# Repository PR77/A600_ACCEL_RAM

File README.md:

# A600_ACCEL_RAM
Design attempt for an Amiga 600 over CPU (PLCC) 68000 Accelerator including 1.5MB FastRAM (... or is it SlowRAM) and 0.5MB MapROM support.

# Warning
This design has not been compliance tested and will not be. It may cause damage to your A600. I take no responsibility for this. I accept no responsibility for any damage to any equipment that results from the use of this design and its components. IT IS ENTIRELY AT YOUR OWN RISK!

# Overview
The main purpose of this design was to develop a simple, affordable and efficient Accelerator, FastRAM and MapROM support device for the Amiga 600. The main components of the design and the CPU (MC68SEC000), CPLD (9572) and SRAM (CY62167G). There are the odd LEDs for status and some IO Pins for currently unplanned additions. As discovered in my A500 Accelerator the MC68SEC000 can be aggressively clocked and this design does not detour from that.

### Appearance
Nice 3D model:

Installed on A600 Motherboard:

Mounting holes on the Accelerator PCB match with the HDD cradle and accommodate a M2 screw to provide stress relief for the PLCC68 socket. SukkoPera has a great guide on how to prepare the PLCC68 socket as some small modifications are required. His how to guide is linked here;

https://github.com/SukkoPera/OpenAmiga600FastRamExpansion/blob/master/SocketRework.md

### Performance
Testing has shown that the A600 system is fairly stable at 40MHz. Slower crystals can be used if stability is an issue (let me know if you run into issues). I've had the classic Amiga Juggler running for 48 Hours without any issues. Classic SysInfo shows @ 40MHz (with MapROM active);

* Drystones: 3448
* MIPS: 3.59
* Comment: Only Amiga Makes.. 

IDE (via GAYLE's scsi.device) also shows a nice speed improvement with a CF Card:

### BOM
For those wanting to build their own hardware, here is the BOM;

| Reference(s)  | Value           | Footprint                                        |
|---------------|-----------------|--------------------------------------------------|
|C1             | 100n            |Capacitors_SMD:C_0805
|C2             | 100n            |Capacitors_SMD:C_0805
|C3             | 100n            |Capacitors_SMD:C_0805
|C4             | 100n            |Capacitors_SMD:C_0805
|C6             | 10u             |Capacitors_Tantalum_SMD:CP_Tantalum_Case-R_EIA-2012-12_Hand
|C7             | 10u             |Capacitors_Tantalum_SMD:CP_Tantalum_Case-R_EIA-2012-12_Hand
|C8             | 100n            |Capacitors_SMD:C_0805
|C9             | 100n            |Capacitors_SMD:C_0805
|C10            | 100n            |Capacitors_SMD:C_0805
|D1             | LED             |LEDs:LED_0805
|D2             | LED             |LEDs:LED_0805
|J1             | JTAG            |Connector:Conn_01x06_Male","Pin_Headers:Pin_Header_Straight_1x06_Pitch2.54mm
|J2 (not loaded)| SPARE1          |Connector:Conn_01x03_Male","Pin_Headers:Pin_Header_Straight_1x03_Pitch2.54mm
|J3 (not loaded)| SPARE2          |Connector:Conn_01x03_Male","Pin_Headers:Pin_Header_Straight_1x03_Pitch2.54mm
|R1             | 10K             |Resistors_SMD:R_0805
|R3             | 10K             |Resistors_SMD:R_0805
|R4             | 10K             |Resistors_SMD:R_0805
|R5             | 10K             |Resistors_SMD:R_0805
|R6             | 10K             |Resistors_SMD:R_0805
|R7             | 10K             |Resistors_SMD:R_0805
|R8 (not loaded)| 10K             |Resistors_SMD:R_0805
|R9             | 10K             |Resistors_SMD:R_0805
|R10            | 680R            |Resistors_SMD:R_0805
|R11            | 680R            |Resistors_SMD:R_0805
|U1             | SOCKET          |PLCC-68_THT-SocketUpsideDown
|U2             | MC68SEC000      |Housings_QFP:LQFP-64_14x14mm_Pitch0.8mm
|U3             | CY62167G        |Housings_SSOP:TSOP-I-48_18.4x12mm_Pitch0.5mm
|U4             | XC9572VQ44      |Housings_QFP:LQFP-44_10x10mm_Pitch0.8mm
|U5             | LM1117-3.3      |TO_SOT_Packages_SMD:SOT-223-3_TabPin2
|X1             | CXO_DIP14       |Oscillators:Oscillator_DIP-14

### CPU
Regarding the CPU, I purchased from here (I get nothing from this. The parts I received were new and legitimate so I wanted to share the source);

https://www.ebay.de/itm/MC68SEC000FU20-IC-MPU-M680X0-20MHZ-64QFP-NEW/311524970603?hash=item488855d06b:g:qe0AAOSwYIhWleGF

### LED Indicators
2 LED indicators are present:

* ACCEL ACTIVE: This indicates that a Bus Request (BR) was requested by the MC68SEC000 Accelerator CPU and Granted (/BG) by the Amiga's MC68000 CPU.
* MAPROM ACTIVE: After writing a 512K MapROM image to the Accelerator, the next subsequent Reset will active this image. This LED indicates that the MapROM image is in use.

### FastRAM (... or is it SlowRAM)
To simplify the design and keep the CPLD pin count down, I decided not to use traditional FastRAM, rather use SlowRAM which is automatically mapped by the Amiga if valid memory is detected between 0xC00000 - 0xD7FFFF. In this range 1.5MB is available. In this memory range, the Accelerator performs the address decoding and subsequent /DTACK cycle. /AS is not asserted on the Amiga, thus the speed of memory cycles in this range is equivalent to that of FastRAM.

### MapROM
Of the 2MB RAM available, 1.5MB is allocated to SlowRAM and the remainder is allocated for MapROM. MapROM simply works by routing write cycle to 0xF8xxxx directly to the Accelerators RAM. Once enough write cycles are detected (262144 WORD writes), the MapROM write status is latched. After a subsequent Reset, memory accesses to 0xF8xxxx are directly routed to the Accelerators RAM (at full speed) and /AS is not asserted on the Amiga.

To deactive MapROM, simply hold down CTRL-A-A for 1 second and it will be deactivated. A different image could then be loaded. Note, once an image is loaded it needs to be deactivated again before a different image can be used. DiagROM images could also be used - helpful to avoid swapping out the physical ROM chip.

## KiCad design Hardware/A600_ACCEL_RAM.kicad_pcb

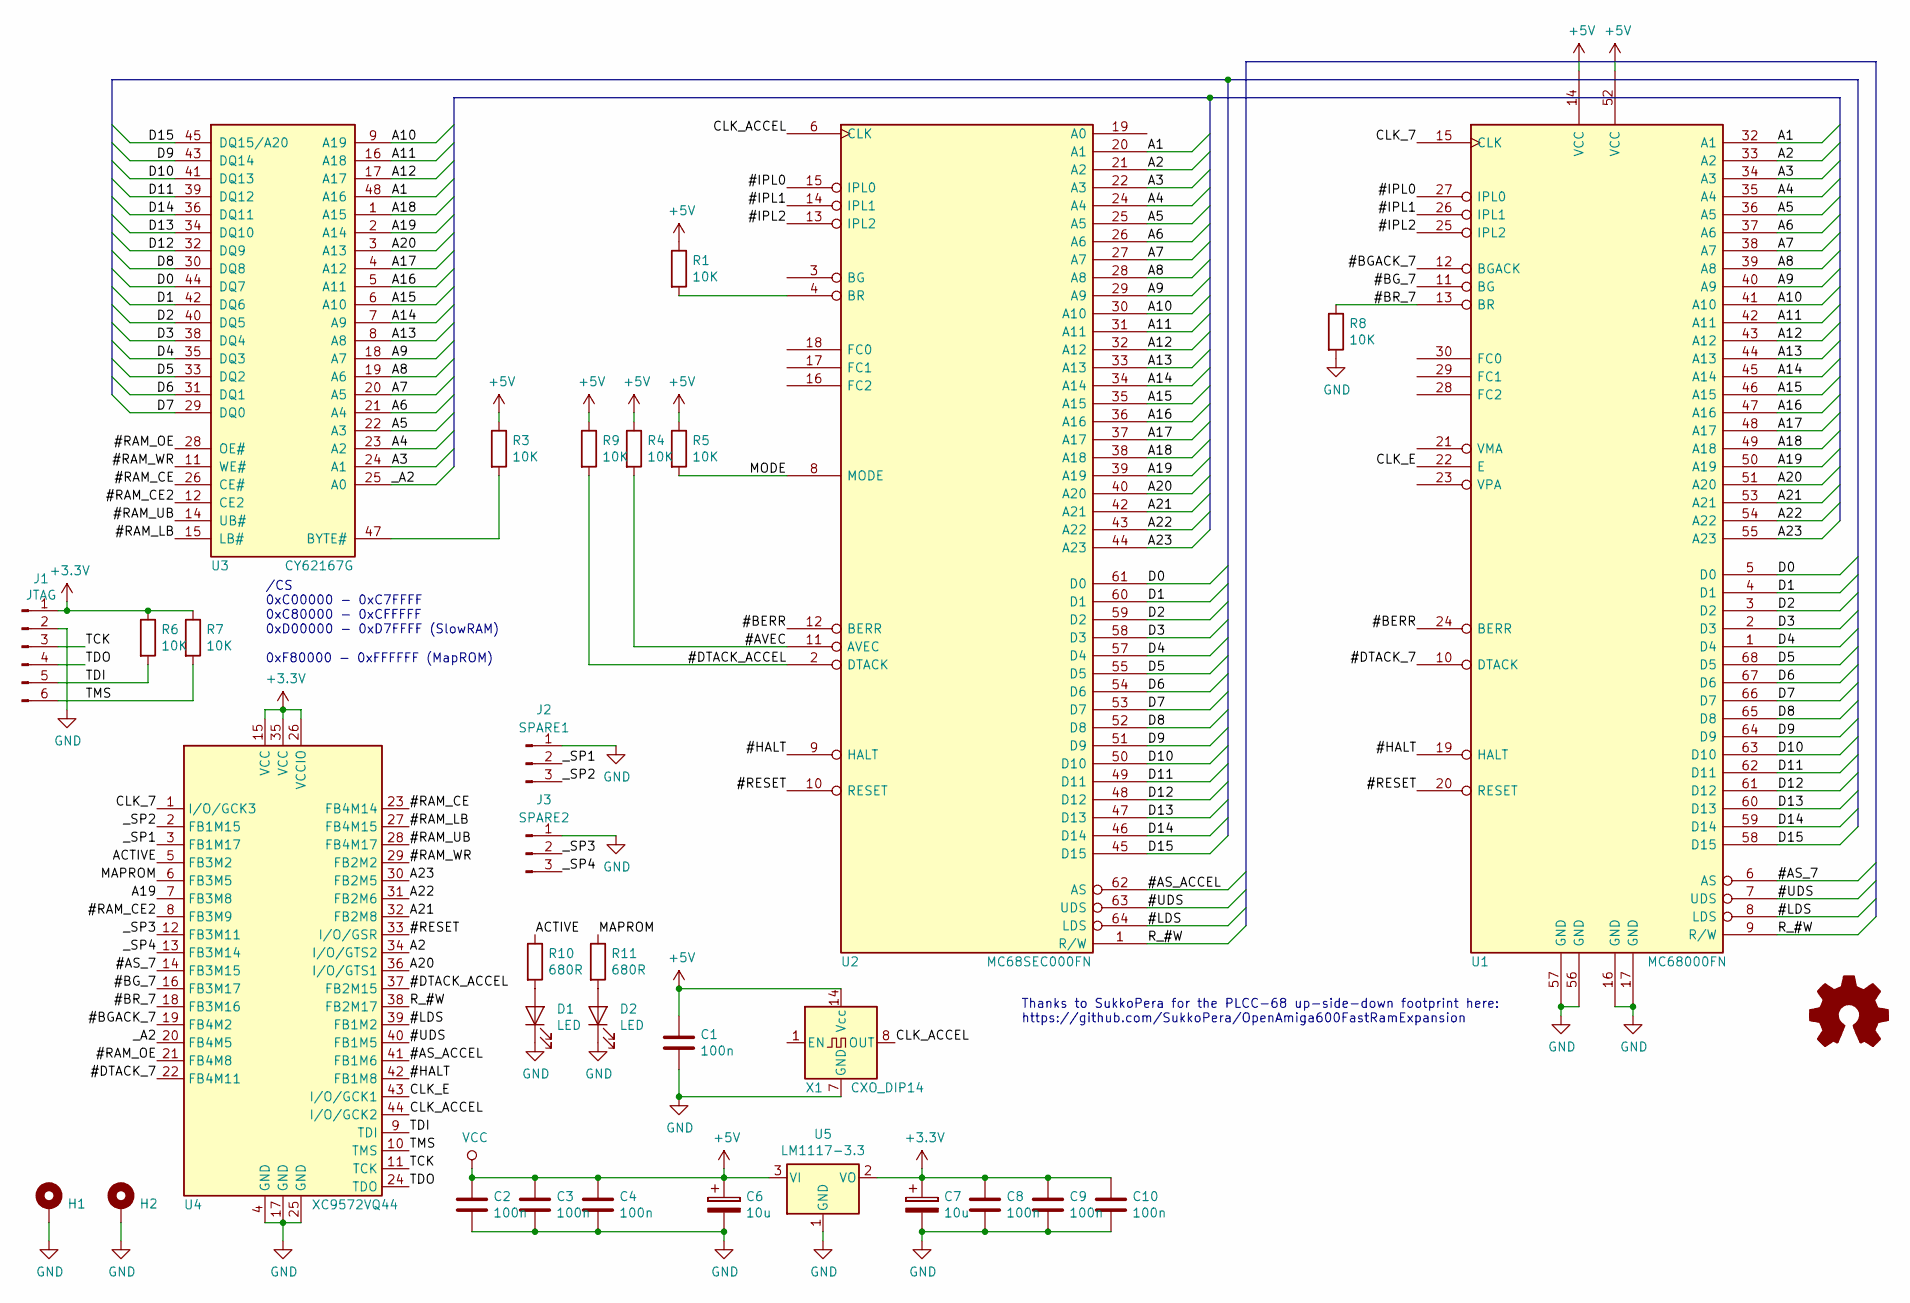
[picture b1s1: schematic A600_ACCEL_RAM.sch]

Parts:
C1, C2, C3, C4, C8, C9, C10: 100n; C_0805
C6, C7: 10u; CP_Tantalum_Case-R_EIA-2012-12_Hand
D1, D2: LED; LED_0805
H1, H2: MountingHole_Pad; MountingHole_2.2mm_M2_Pad_Via
J1: JTAG; Pin_Header_Straight_1x06_Pitch2.54mm
J2: SPARE1; Pin_Header_Straight_1x03_Pitch2.54mm
J3: SPARE2; Pin_Header_Straight_1x03_Pitch2.54mm
LOGO1: OSHW; OSHW-Symbol_6.7x6mm_SilkScreen
R1, R3, R4, R5, R6, R7, R8, R9: 10K; R_0805
R10, R11: 680R; R_0805
U1: MC68000FN; PLCC-68_THT-SocketUpsideDown
U2: MC68SEC000FN; LQFP-64_14x14mm_Pitch0.8mm
U3: CY62167G; TSOP-I-48_18.4x12mm_Pitch0.5mm
U4: XC9572VQ44; LQFP-44_10x10mm_Pitch0.8mm
U5: LM1117-3.3; SOT-223-3_TabPin2
X1: CXO_DIP14; Oscillator_DIP-14

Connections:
+3V3: C7.1, C8.1, C9.1, C10.1, J1.1, R6.1, R7.1, U4.15 (VCC), U4.26 (VCCIO), U4.35 (VCC), U5.2 (VO)
+5V: C1.1, C2.1, C3.1, C4.1, C6.1, R1.1, R3.1, R4.1, R5.1, R9.1, U1.14 (VCC), U1.52 (VCC), U2.5 (VCC), U2.41 (VCC), U3.37 (VCC), U5.3 (VI), X1.14 (Vcc)
/#AS_7: U1.6 (AS), U4.14 (FB3M15)
/#AS_ACCEL: U2.62 (AS), U4.41 (FB1M6)
/#AVEC: R4.2, U2.11 (AVEC)
/#BERR: U1.24 (BERR), U2.12 (BERR)
/#BGACK_7: U1.12 (BGACK), U4.19 (FB4M2)
/#BG_7: U1.11 (BG), U4.16 (FB3M17)
/#BR_7: R8.1, U1.13 (BR), U4.18 (FB3M16)
/#DTACK_7: U1.10 (DTACK), U4.22 (FB4M11)
/#DTACK_ACCEL: R9.2, U2.2 (DTACK), U4.37 (FB2M15)
/#HALT: U1.19 (HALT), U2.9 (HALT), U4.42 (FB1M8)
/#IPL0: U1.27 (IPL0), U2.15 (IPL0)
/#IPL1: U1.26 (IPL1), U2.14 (IPL1)
/#IPL2: U1.25 (IPL2), U2.13 (IPL2)
/#LDS: U1.8 (LDS), U2.64 (LDS), U4.39 (FB1M2)
/#RAM_CE: U3.26 (CE#), U4.23 (FB4M14)
/#RAM_CE2: U3.12 (CE2), U4.8 (FB3M9)
/#RAM_LB: U3.15 (LB#), U4.27 (FB4M15)
/#RAM_OE: U3.28 (OE#), U4.21 (FB4M8)
/#RAM_UB: U3.14 (UB#), U4.28 (FB4M17)
/#RAM_WR: U3.11 (WE#), U4.29 (FB2M2)
/#RESET: U1.20 (RESET), U2.10 (RESET), U4.33 (I/O/GSR)
/#UDS: U1.7 (UDS), U2.63 (UDS), U4.40 (FB1M5)
/A1: U1.32 (A1), U2.20 (A1), U3.48 (A16)
/A2: U1.33 (A2), U2.21 (A2), U4.34 (I/O/GTS2)
/A3: U1.34 (A3), U2.22 (A3), U3.24 (A1)
/A4: U1.35 (A4), U2.24 (A4), U3.23 (A2)
/A5: U1.36 (A5), U2.25 (A5), U3.22 (A3)
/A6: U1.37 (A6), U2.26 (A6), U3.21 (A4)
/A7: U1.38 (A7), U2.27 (A7), U3.20 (A5)
/A8: U1.39 (A8), U2.28 (A8), U3.19 (A6)
/A9: U1.40 (A9), U2.29 (A9), U3.18 (A7)
/A10: U1.41 (A10), U2.30 (A10), U3.9 (A19)
/A11: U1.42 (A11), U2.31 (A11), U3.16 (A18)
/A12: U1.43 (A12), U2.32 (A12), U3.17 (A17)
/A13: U1.44 (A13), U2.33 (A13), U3.8 (A8)
/A14: U1.45 (A14), U2.34 (A14), U3.7 (A9)
/A15: U1.46 (A15), U2.35 (A15), U3.6 (A10)
/A16: U1.47 (A16), U2.36 (A16), U3.5 (A11)
/A17: U1.48 (A17), U2.37 (A17), U3.4 (A12)
/A18: U1.49 (A18), U2.38 (A18), U3.1 (A15)
/A19: U1.50 (A19), U2.39 (A19), U3.2 (A14), U4.7 (FB3M8)
/A20: U1.51 (A20), U2.40 (A20), U3.3 (A13), U4.36 (I/O/GTS1)
/A21: U1.53 (A21), U2.42 (A21), U4.32 (FB2M8)
/A22: U1.54 (A22), U2.43 (A22), U4.31 (FB2M6)
/A23: U1.55 (A23), U2.44 (A23), U4.30 (FB2M5)
/ACTIVE: R10.1, U4.5 (FB3M2)
/CLK_7: U1.15 (CLK), U4.1 (I/O/GCK3)
/CLK_ACCEL: U2.6 (CLK), U4.44 (I/O/GCK2), X1.8 (OUT)
/CLK_E: U1.22 (E), U4.43 (I/O/GCK1)
/D0: U1.5 (D0), U2.61 (D0), U3.44 (DQ7)
/D1: U1.4 (D1), U2.60 (D1), U3.42 (DQ6)
/D2: U1.3 (D2), U2.59 (D2), U3.40 (DQ5)
/D3: U1.2 (D3), U2.58 (D3), U3.38 (DQ4)
/D4: U1.1 (D4), U2.57 (D4), U3.35 (DQ3)
/D5: U1.68 (D5), U2.55 (D5), U3.33 (DQ2)
/D6: U1.67 (D6), U2.54 (D6), U3.31 (DQ1)
/D7: U1.66 (D7), U2.53 (D7), U3.29 (DQ0)
/D8: U1.65 (D8), U2.52 (D8), U3.30 (DQ8)
/D9: U1.64 (D9), U2.51 (D9), U3.43 (DQ14)
/D10: U1.63 (D10), U2.50 (D10), U3.41 (DQ13)
/D11: U1.62 (D11), U2.49 (D11), U3.39 (DQ12)
/D12: U1.61 (D12), U2.48 (D12), U3.32 (DQ9)
/D13: U1.60 (D13), U2.47 (D13), U3.34 (DQ10)
/D14: U1.59 (D14), U2.46 (D14), U3.36 (DQ11)
/D15: U1.58 (D15), U2.45 (D15), U3.45 (DQ15/A20)
/MAPROM: R11.1, U4.6 (FB3M5)
/MODE: R5.2, U2.8 (MODE)
/R_#W: U1.9 (R/W), U2.1 (R/W), U4.38 (FB2M17)
/TCK: J1.3, U4.11 (TCK)
/TDI: J1.5, R6.2, U4.9 (TDI)
/TDO: J1.4, U4.24 (TDO)
/TMS: J1.6, R7.2, U4.10 (TMS)
/_A2: U3.25 (A0), U4.20 (FB4M5)
/_SP1: J2.2, U4.3 (FB1M17)
/_SP2: J2.3, U4.2 (FB1M15)
/_SP3: J3.2, U4.12 (FB3M11)
/_SP4: J3.3, U4.13 (FB3M14)
GND: C1.2, C2.2, C3.2, C4.2, C6.2, C7.2, C8.2, C9.2, C10.2, D1.1 (K), D2.1 (K), H1.1, H2.1, J1.2, J2.1, J3.1, R8.2, U1.16 (GND), U1.17 (GND), U1.56 (GND), U1.57 (GND), U2.7 (GND), U2.23 (GND), U2.56 (GND), U3.27 (GND), U3.46 (GND), U4.4 (GND), U4.17 (GND), U4.25 (GND), U5.1 (GND), X1.7 (GND)
unnamed: D1.2 (A), R10.2
unnamed: D2.2 (A), R11.2
unnamed: R1.2, U2.4 (BR)
unnamed: R3.2, U3.47 (BYTE#)

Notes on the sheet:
Thanks to SukkoPera for the PLCC-68 up-side-down footprint here: https://github.com/SukkoPera/OpenAmiga600FastRamExpansion
/CS 0xC00000 - 0xC7FFFF 0xC80000 - 0xCFFFFF 0xD00000 - 0xD7FFFF (SlowRAM) 0xF80000 - 0xFFFFFF (MapROM)

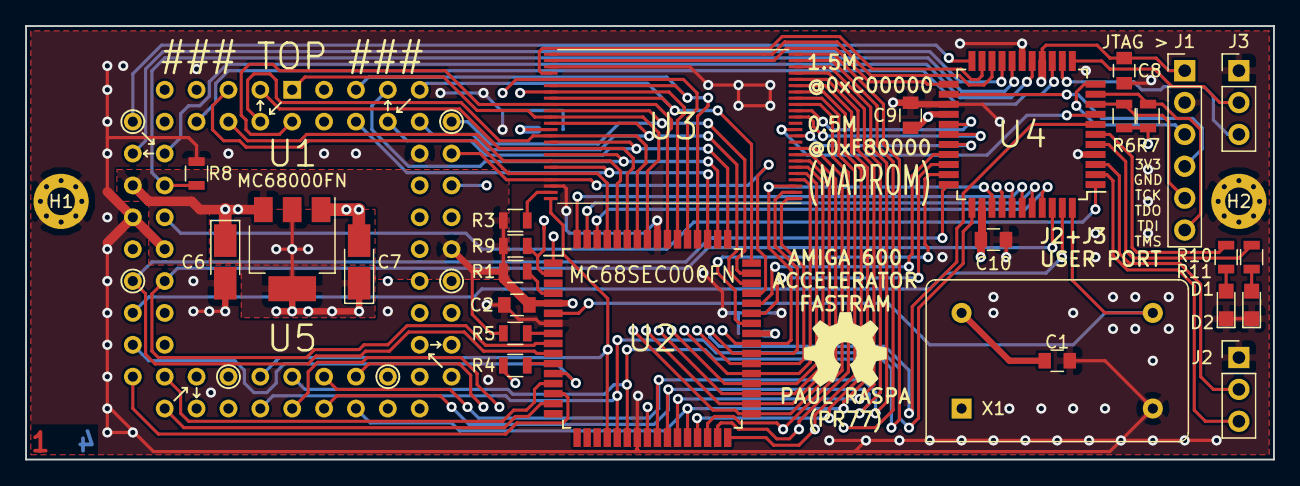
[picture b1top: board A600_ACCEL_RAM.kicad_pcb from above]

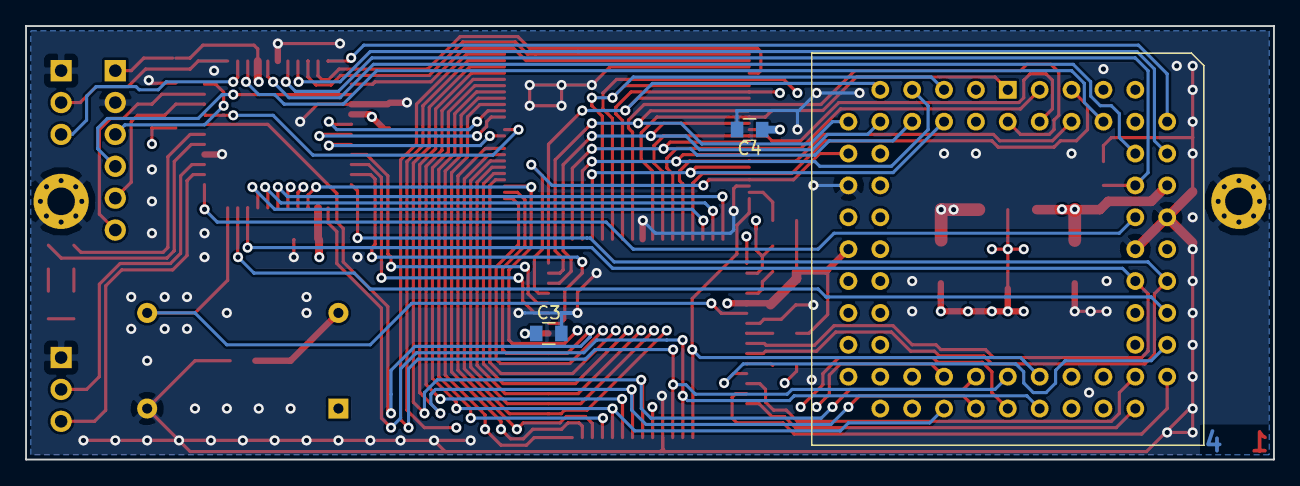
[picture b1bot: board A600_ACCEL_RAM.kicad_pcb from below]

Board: 4 copper layers, 99.4 x 34.5 mm, 33 parts (2 on the bottom side), 84 nets.

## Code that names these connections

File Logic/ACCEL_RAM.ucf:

#PACE: Start of Constraints generated by PACE

#PACE: Start of PACE I/O Pin Assignments
NET "_A2"  LOC = "P20"  ;
NET "A2"  LOC = "P34"  ;
NET "ACCEL_ACTIVE"  LOC = "P5"  ; 
NET "ADDRESS<19>"  LOC = "P7"  ; 
NET "ADDRESS<20>"  LOC = "P36"  ;
NET "ADDRESS<21>"  LOC = "P32"  ;
NET "ADDRESS<22>"  LOC = "P31"  ;
NET "ADDRESS<23>"  LOC = "P30"  ;
NET "AS_7"  LOC = "P14"  ; 
NET "AS_ACCEL"  LOC = "P41"  ;
NET "BG_7"  LOC = "P16"  ; 
NET "BGACK_7"  LOC = "P19"  ; 
NET "BR_7"  LOC = "P18"  ; 
NET "CLK_7"  LOC = "P1"  ; 
NET "CLK_ACCEL"  LOC = "P44"  ;
NET "CLK_E"  LOC = "P43"  ;
NET "DTACK_7"  LOC = "P22"  ;
NET "DTACK_ACCEL"  LOC = "P37"  ;
NET "HALT"  LOC = "P42"  ;
NET "IO_PORT<0>"  LOC = "P3"  ; 
NET "IO_PORT<1>"  LOC = "P2"  ; 
NET "IO_PORT<2>"  LOC = "P12"  ; 
NET "IO_PORT<3>"  LOC = "P13"  ; 
NET "LDS"  LOC = "P39"  ;
NET "MAPROM_ACTIVE"  LOC = "P6"  ; 
NET "r_RAM_CE2"  LOC = "P8"  ;
NET "r_RAM_CE_n"  LOC = "P23"  ;
NET "r_RAM_LB_n"  LOC = "P27"  ;
NET "r_RAM_OE_n"  LOC = "P21"  ;
NET "r_RAM_UB_n"  LOC = "P28"  ;
NET "r_RAM_WR_n"  LOC = "P29"  ;
NET "RESET"  LOC = "P33"  ;
NET "RW"  LOC = "P38"  ;
NET "UDS"  LOC = "P40"  ;

#PACE: Start of PACE Area Constraints

#PACE: Start of PACE Prohibit Constraints

#PACE: End of Constraints generated by PACE

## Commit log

2021-01-17 Updates
    First commit of complete design.
2021-01-29 Updates
    Added link to howto for the PLCC68 modifications.
2021-02-21 Updates
    Added JED for 30MHz and Verilog.
2025-06-30 Delete Logic/_xmsgs directory
    Removed superfluous content.
2025-06-30 Updates
    Project files updates.
2025-07-06 Updates
    Project maintenance updates.
2025-10-25 Updates
    Added 'define for enabling (or disabling) 1WS on FASTRAM accesses.
